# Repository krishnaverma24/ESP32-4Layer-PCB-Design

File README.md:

# ESP32 All-Sensor Board (4-Layer PCB Design)

## 📖 Overview
This repository contains the design files for a custom 4-layer PCB integrating the ESP32 microcontroller with multiple sensors and supporting circuits.  
The board is designed as a compact all-in-one sensor platform for IoT and embedded system experiments. It includes sensor interfaces, amplifier circuits, and a regulated power section, making it suitable for real-world prototyping and academic projects.

---

## ⚙️ Features
- **ESP32 Microcontroller**
  - Dual-core processor with Wi-Fi + Bluetooth
  - GPIO breakout pins for external modules
- **Integrated Sensors**
  - BMP90 sensor for pressure and temperature measurement
  - Humidity sensor interface for environmental monitoring
- **Amplifier System**
  - Signal conditioning stage for sensor outputs
  - Designed for clean analog-to-digital conversion
- **Power Section**
  - LDO-based regulation for 3.3V and 5V rails
  - Separate copper planes for power and ground
  - Decoupling capacitors for noise reduction
- **PCB Design**
  - 4-layer stack-up for optimized routing
  - Dedicated copper planes for stability
  - Compact layout with clear separation of analog and digital sections

---

## 📂 Repository Contents
- **/schematics** → Circuit schematic files (`.sch`, `.pdf`)
- **/pcb_layout** → PCB design files (`.kicad_pcb`, EasyEDA exports)
- **/gerber** → Gerber files for fabrication
- **/images** → PCB screenshots (top layer, bottom layer, 3D view)
- **README.md** → Project description and usage details

---

## 🖼️ PCB Views

---

## 🚀 Tools Used
- **EasyEDA** → schematic & PCB design
- **KiCad** → verification and cross-checking
- **Standard PCB workflow** → Gerber export for manufacturing

---

## 🎯 Applications
- IoT sensor fusion projects
- Environmental monitoring (temperature, humidity, pressure)
- Embedded system prototyping with ESP32
- Signal conditioning experiments with amplifier circuits
- Academic learning for PCB design and hardware integration

---

## 🛠 How to Use
1. Clone this repository  
2. Open schematic files in EasyEDA/KiCad  
3. Review PCB layout and modify if needed  
4. Use Gerber files for fabrication  
5. Assemble components and test sensor outputs with ESP32 firmware  

---

## 📌 Future Improvements
- Add more sensors (gas, accelerometer, gyroscope)  
- Improve amplifier stage for higher accuracy  
- Add USB-C power input and charging circuit  
- Integrate OLED display for real-time sensor data  

---

## 📜 License
This project is licensed under the **MIT License** – feel free to use, modify, and share with proper credit.

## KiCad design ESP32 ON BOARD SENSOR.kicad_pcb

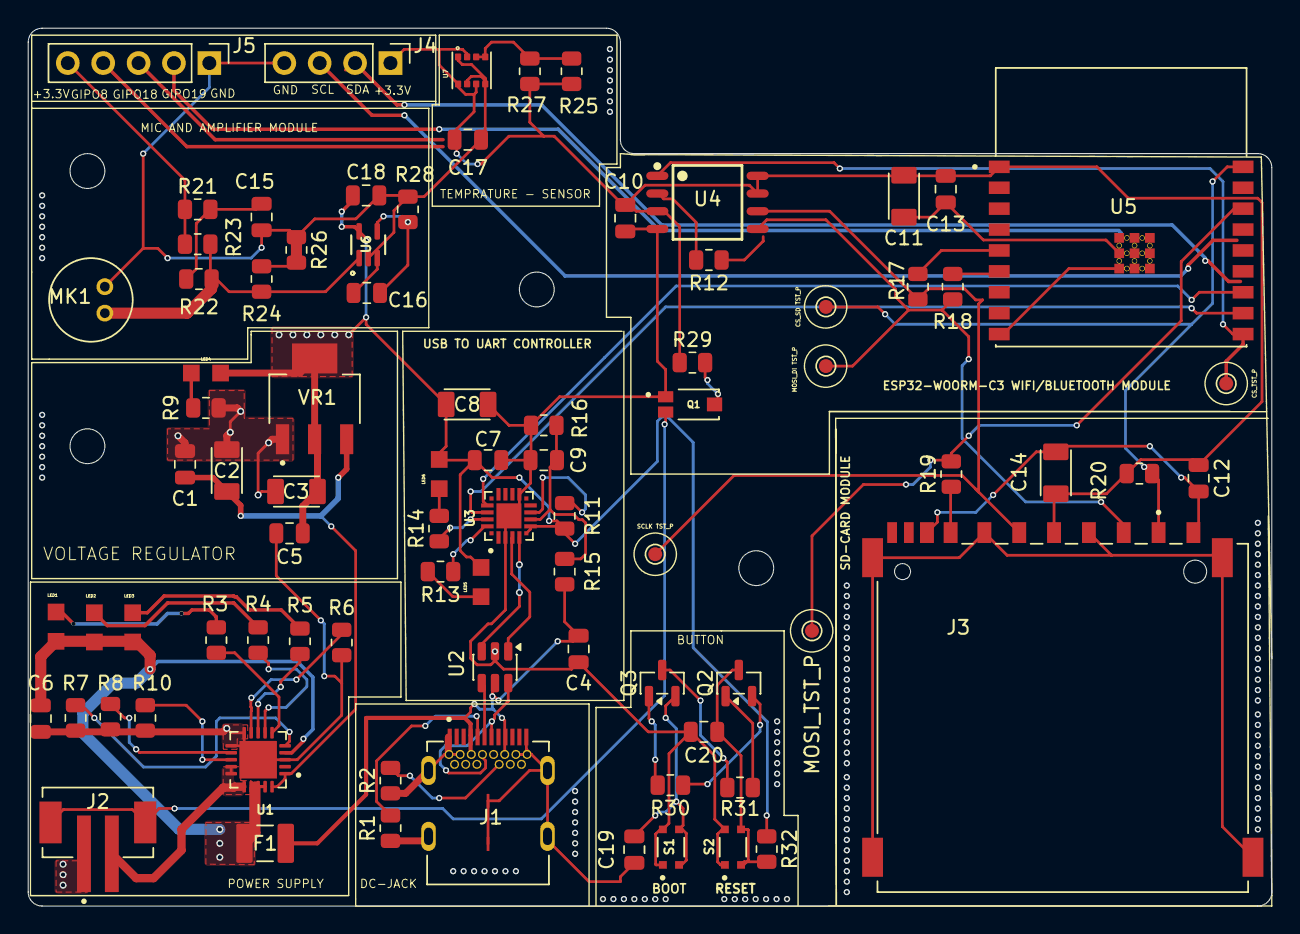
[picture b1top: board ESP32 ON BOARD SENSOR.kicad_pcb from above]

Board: 4 copper layers, 89.2 x 63.0 mm, 83 parts (0 on the bottom side), 52 nets.

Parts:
C1: 0,1uF; C_0805_2012Metric
C2, C3, C13, C14: 10uF; RESC3216X125N
C4, C5, C7, C10, C11, C12, C15, C16, C17, C18, C19: 0.1uF; C_0805_2012Metric
C6, C9, C20: 1uF; C_0805_2012Metric
C8: 4.7uF; RESC3216X125N
CS_TST_P: Test CS; TestPoint_Pad_D1.0mm
F1: 0ZCH0110AF2E; FUSC3225X100N
J1: SS-52400-003; BELFUSE_SS-52400-003
J2: B2B-PH-SM4-TB; JST_B2B-PH-SM4-TB
J3: GSD090012SEU; AMPHENOL_GSD090012SEU
J4: Conn_01x04_Pin; PinHeader_1x04_P2.54mm_Vertical
J5: Conn_01x05_Pin; PinHeader_1x05_P2.54mm_Vertical
LED1, LED2, LED3, LED4, LED5, LED6: LTST-C170KRKT; DIOC200X125X110
MK1: CMC-5042PF-AC; CUI_CMC-5042PF-AC
MOSI_TST_P: Test MOSI_DO; TestPoint_Pad_D1.0mm
Q1: TEMT6000X01; TRANS_TEMT6000X01
Q2, Q3: BC817; SOT-23
R1, R2: 5K1; R_0805_2012Metric
R3, R4, R5, R9, R13, R14: 470; R_0805_2012Metric
R6, R7: 10k; R_0805_2012Metric
R8: 20K; R_0805_2012Metric
R10, R21, R22: 2K; R_0805_2012Metric
R11: 1K; R_0805_2012Metric
R12, R17, R18, R19: 50; R_0805_2012Metric
R15: 22K1; R_0805_2012Metric
R16: 47K5; R_0805_2012Metric
R20, R26, R30, R31, R32: 10K; R_0805_2012Metric
R23, R24: 1M; R_0805_2012Metric
R25, R27: 4K7; R_0805_2012Metric
R28: 100K; R_0805_2012Metric
R29: R; R_0805_2012Metric
S1: BOOT; SW_USLPT2819DT2TR
S2: RESET; SW_USLPT2819DT2TR
TP1: Test MOSI_DI; TestPoint_Pad_D1.0mm
TP3: Test SCLK; TestPoint_Pad_D1.0mm
TP4: Test CS_SD; TestPoint_Pad_D1.0mm
U1: MCP73871-2CAI_ML; QFN50P400X400X100-21N
U2: USBLC6-2SC6; SOT-23-6
U3: CP2102N-A02-GQFN20R; SILABS_CP2102N-A02-GQFN20R
U4: W25Q32JVSSIQ; SOIC127P790X216-8N
U5: ESP32-C3-WROOM-02-H4; MODULE_ESP32-C3-WROOM-02-H4
U6: MAX4466EXK; SOT65P210X110-5N
U7: BME280; PSON65P250X250X100-8N
VR1: LM1117MPX-3.3; VREG_LM1117MPX-3.3

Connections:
+3.3V: C3.1, C5.1, C7.1, C8.2, C10.1, C11.1, C12.1, C13.1, C14.1, C17.1, C18.1, J3.4 (VDD1), J4.1, J5.5, LED4.+, LED5.+, LED6.+, R11.1, R20.1, R21.1, R23.1, R25.1, R27.1, R29.1, R32.1, U3.6 (VDD), U3.7 (VREGIN), U4.3 (~WP(IO2)), U4.7 (~HOLD/~RESET(IO3)), U4.8 (VCC), U5.1 (3V3), U6.5 (VCC), U7.2 (CSB), U7.6 (VDDIO), U7.8 (VDD), VR1.2 (VOUT_2), VR1.4 (VOUT_4)
+5V: C1.1, C2.1, U1.1 (OUT), U1.20 (OUT), VR1.3 (VIN)
/+5V_USB: C6.2, F1.1, LED1.+, LED2.+, LED3.+, U1.2 (VPCC), U1.4 (PROG2), U1.17 (CE), U1.18 (IN), U1.19 (IN)
/CHARGED: R5.1, U1.8 (STAT1/~LBO)
/CHARGING: LED1.-, R3.2
/CHARGING_POWER_GOOD: R4.1, U1.7 (STAT2)
/ESP32-C3-02/CD_SD: J3.1 (CD/DAT3), R20.2, TP4.1 (1_1), U5.18 (IO0)
/ESP32-C3-02/CS: CS_TST_P.1 (1_1), U4.1 (~CS), U5.10 (IO10)
/ESP32-C3-02/MISO_DO: MOSI_TST_P.1 (1_1), R19.2, U5.16 (IO2)
/ESP32-C3-02/MOSI_DI: J3.2 (CMD), R18.2, TP1.1 (1_1), U4.5 (DI(IO0))
/ESP32-C3-02/RX_TX: U3.17 (RXD), U5.12 (TXD)
/ESP32-C3-02/SCLK: J3.5 (CLK), R17.1, TP3.1 (1_1), U4.6 (CLK)
/ESP32-C3-02/SENSORS/MIC_OUT: C16.2, R28.2, U6.4 (OUT)
/ESP32-C3-02/SENSORS/PHOTO_C: Q1.3, R29.2
/ESP32-C3-02/SENSORS/SCL: R25.2, R27.2, U7.3 (SDI), U7.4 (SCK)
/ESP32-C3-02/TX_RX: U3.18 (TXD), U5.11 (RXD)
/ESP32-C3-02/USB_D+: U2.3 (I/O2), U3.5 (D-)
/ESP32-C3-02/USB_D-: U2.1 (I/O1), U3.4 (D+)
/ESP32-C3-02/USER_INTERFACE/BOOT: C19.1, Q3.2 (E), S1.3, S1.4
/ESP32-C3-02/USER_INTERFACE/DTR: Q3.3 (C), R31.1
/ESP32-C3-02/USER_INTERFACE/EN: C20.1, Q2.3 (C), R32.2, S2.3, S2.4
/ESP32-C3-02/USER_INTERFACE/RTS: Q2.2 (E), R30.1
/USB_DN: J1.A7 (DN1), J1.B7 (DN2), U2.6 (I/O1)
/USB_DP: J1.A6 (DP1), J1.B6 (DP2), U2.4 (I/O2)
/VBAT: J2.2, U1.14 (VBAT), U1.15 (VBAT), U1.16 (VBAT_SENSE)
/VBUS: C4.1, F1.2, J1.A4 (VBUSA1), J1.A9 (VBUSA2), J1.B4 (VBUSB1), J1.B9 (VBUSB2), R15.1, U2.5 (VBUS)
GND: C1.2, C2.2, C3.2, C4.2, C5.2, C6.1, C7.2, C8.1, C9.2, C10.2, C11.2, C12.2, C13.2, C14.2, C15.1, C16.1, C17.2, C18.2, C19.2, C20.2, J1.A1 (GNDA1), J1.A12 (GNDA2), J1.B1 (GNDB1), J1.B12 (GNDB2), J1.G1 (GND/SHIELD), J1.G2 (GND/SHIELD), J1.G3 (GND/SHIELD), J1.G4 (GND/SHIELD), J1.S1 (GND/SHIELD), J1.S2 (GND/SHIELD), J1.S3 (GND/SHIELD), J1.S4 (GND/SHIELD), J2.1, J3.8 (DAT1), J3.9 (DAT2), J4.4, J5.1, MK1.GND, Q1.1, R1.1, R2.1, R6.1, R7.2, R8.2, R9.2, R10.2, R16.2, R24.2, R26.1, R26.2, R28.1, S1.1, S1.2, S2.1, S2.2, U1.3 (SEL), U1.10 (VSS), U1.11 (VSS), U1.21 (VSS), U2.2 (GND), U3.3 (GND), U3.12 (GND), U3.21 (GND), U4.4 (GND), U5.9 (GND), U5.19 (GND), U5.20 (GND), U5.21 (GND), U5.22 (GND), U5.23 (GND), U5.24 (GND), U5.25 (GND), U5.26 (GND), U5.27 (GND), U5.28 (GND), U5.29 (GND), U5.30 (GND), U5.31 (GND), U5.32 (GND), U5.33 (GND), U5.34 (GND), U5.35 (GND), U5.36 (GND), U5.37 (GND), U5.38 (GND), U5.39 (GND), U6.2 (GND), U6.3 (IN-), U7.1 (GND), U7.5 (SDO), U7.7 (GND), VR1.1 (GND)
unnamed: C15.2, R21.2, R22.1
unnamed: J1.A5 (CC1), R1.2
unnamed: J1.B5 (CC2), R2.2
unnamed: J3.7 (DAT0), R19.1
unnamed: LED2.-, R4.2
unnamed: LED3.-, R5.2
unnamed: LED4.-, R9.1
unnamed: LED5.-, R13.2
unnamed: LED6.-, R14.2
unnamed: Q2.1 (B), R31.2
unnamed: Q3.1 (B), R30.2
unnamed: R10.1, U1.13 (PROG1)
unnamed: R8.1, U1.12 (PROG3)
unnamed: R7.1, U1.5 (THERM)
unnamed: R3.1, U1.6 (~PG)
unnamed: R6.2, U1.9 (~TE)
unnamed: R13.1, U3.20 (GPIO.2/TXT)
unnamed: R14.1, U3.19 (GPIO.3/RXT)
unnamed: C9.1, R15.2, R16.1, U3.8 (VBUS)
unnamed: R11.2, U3.9 (~RST)
unnamed: R12.2, U4.2 (DO(IO1))
unnamed: R17.2, U5.5 (IO6)
unnamed: R18.1, U5.6 (IO7)
unnamed: MK1.OUT, R22.2, R23.2, R24.1, U6.1 (IN+)
SHIELD_GND: J3.3 (VSS1), J3.6 (VSS2), J3.G1 (SHIELD_GND), J3.G2 (SHIELD_GND), J3.G3 (SHIELD_GND), J3.G4 (SHIELD_GND)
